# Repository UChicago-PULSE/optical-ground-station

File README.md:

This repository contains files from the Optical Ground Station.
  - Polarimeter Data Collection Contains data obtained from Polarimeter experiments and code to parse that data written by Juan Prieto
  - Telescope Control contains code to control the telescope and point it according to a predetermined path. Written by Rodrigo Spinola e Castro
  - Camera Control will have code to interface with the tracking camera. Written by Ashley Ashiku and Juan Prieto
  - Comparator will have KiCad 9.0 files for the OGS comparator circuit. Designed by Juan Prieto

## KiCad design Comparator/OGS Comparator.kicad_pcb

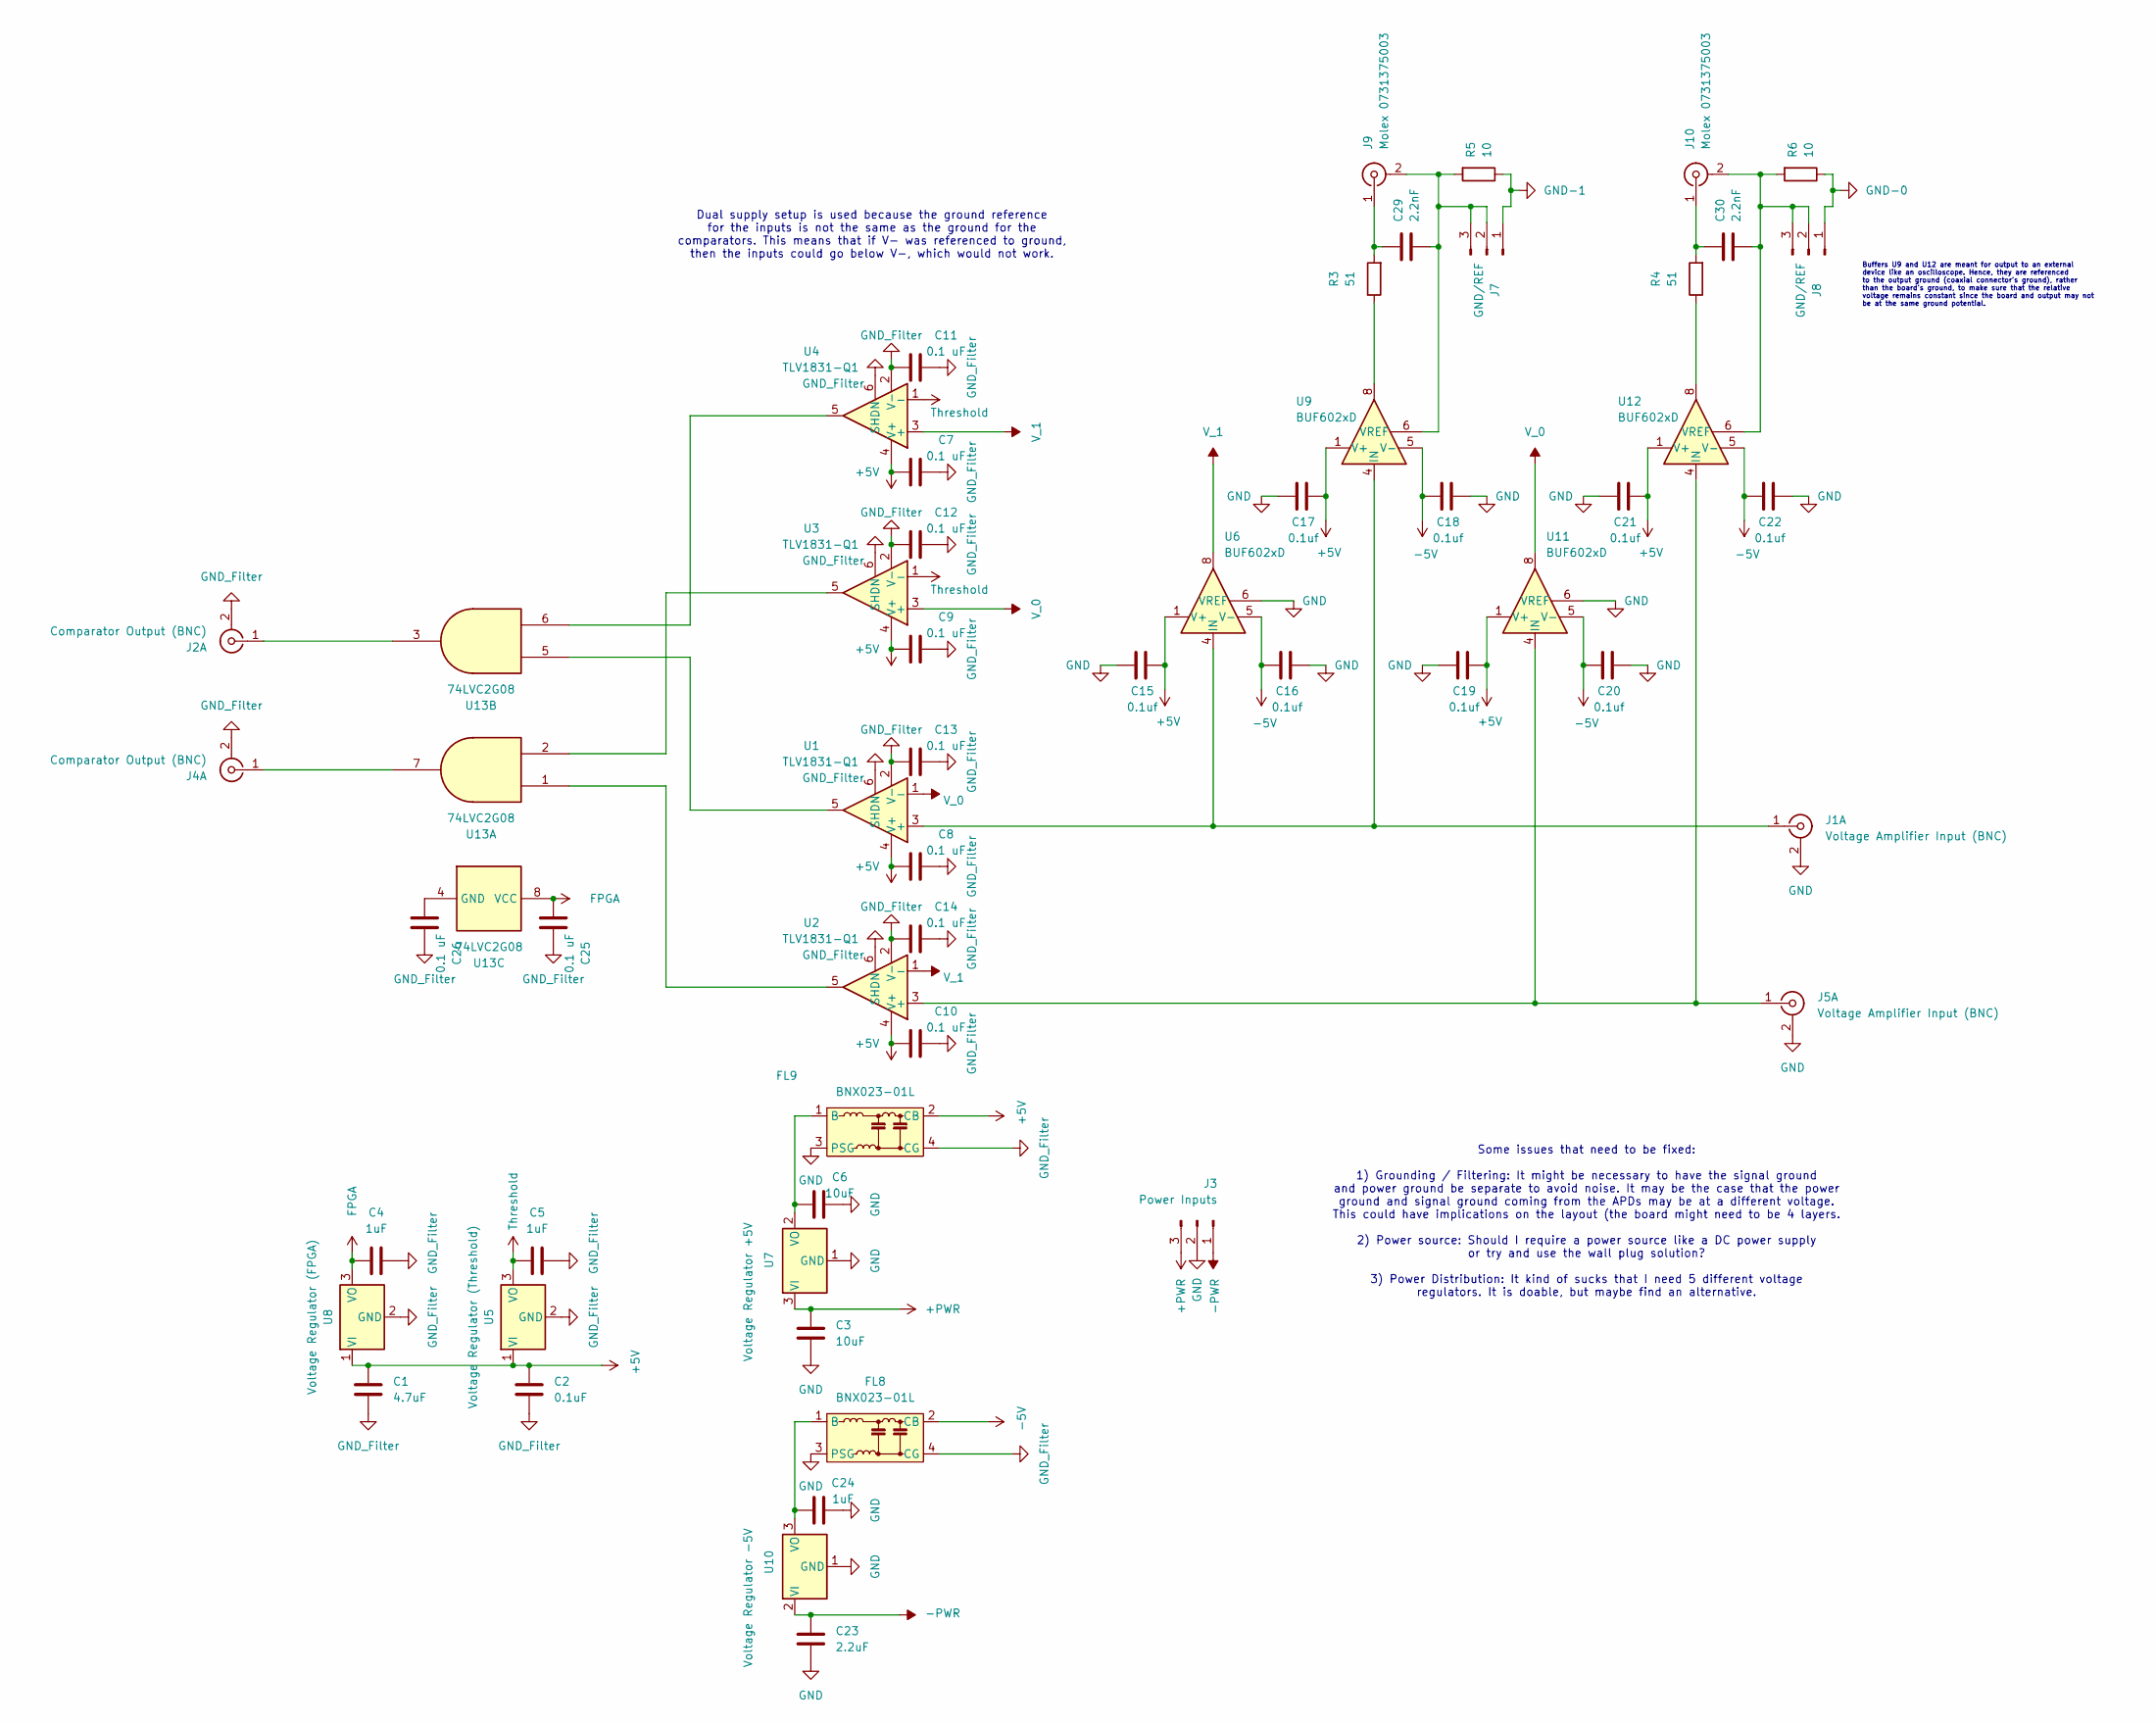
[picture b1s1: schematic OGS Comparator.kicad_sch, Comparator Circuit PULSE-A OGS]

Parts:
C1: 4.7uF; C_0805_2012Metric
C2: 0.1uF; C_0805_2012Metric
C3, C6: 10uF; C_0805_2012Metric
C4, C5, C24: 1uF; C_0805_2012Metric
C7, C8, C9, C10, C11, C12, C13, C14, C25, C26: 0.1 uF; C_0805_2012Metric
C15, C16, C17, C18, C19, C20, C21, C22: 0.1uf; C_0805_2012Metric
C23: 2.2uF; C_0805_2012Metric
C29, C30: 2.2nF; C_0805_2012Metric; LCSC Part # C28260
FL8, FL9: BNX023-01L; Filter_Murata_BNX025
J1, J5: Voltage Amplifier Input (BNC); Molex BNC
J2, J4: Comparator Output (BNC); Molex BNC
J3: Power Inputs; JST_EH_B3B-EH-A_1x03_P2.50mm_Vertical
J7, J8: GND/REF; PinHeader_1x03_P2.54mm_Vertical
J9, J10: Molex 0731375003; Molex BNC
R3, R4: 51; R_0805_2012Metric; LCSC Part # C17738
R5, R6: 10; R_0805_2012Metric; LCSC C25278
U1, U2, U3, U4: TLV1831-Q1; SOT-23-6
U5: Voltage Regulator (Threshold); TO-220-3_Vertical
U6, U9, U11, U12: BUF602xD; SOIC-8_3.9x4.9mm_P1.27mm
U7: Voltage Regulator +5V; TO-220-3_Vertical
U8: Voltage Regulator (FPGA); TO-220-3_Vertical
U10: Voltage Regulator -5V; TO-220-3_Vertical
U13: 74LVC2G08; VSSOP-8_2.3x2mm_P0.5mm

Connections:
+5V: C1.1, C2.1, C7.1, C8.1, C9.1, C10.1, C15.2, C17.2, C19.2, C21.2, FL9.2 (CB), U1.4 (V+), U2.4 (V+), U3.4 (V+), U4.4 (V+), U5.1 (VI), U6.1 (V+), U8.1 (VI), U9.1 (V+), U11.1 (V+), U12.1 (V+)
+PWR: C3.1, J3.3, U7.3 (VI)
-5V: C16.1, C18.1, C20.1, C22.1, FL8.2 (CB), U6.5 (V-), U9.5 (V-), U11.5 (V-), U12.5 (V-)
-PWR: C23.1, J3.1, U10.2 (VI)
FPGA: C4.1, C25.1, U8.3 (VO), U13.8 (VCC)
GND: C3.2, C6.2, C15.1, C16.2, C17.1, C18.2, C19.1, C20.2, C21.1, C22.2, C23.2, C24.2, FL8.3 (PSG), FL9.3 (PSG), J1.2 (Ext1), J3.2, J5.2 (Ext1), U6.6 (VREF), U7.1 (GND), U10.1 (GND), U11.6 (VREF)
GND-0: J8.1, R6.1
GND-1: J7.1, R5.1
GND_Filter: C1.2, C2.2, C4.2, C5.2, C7.2, C8.2, C9.2, C10.2, C11.1, C11.2, C12.1, C12.2, C13.1, C13.2, C14.1, C14.2, C25.2, C26.2, FL8.4 (CG), FL9.4 (CG), J2.2 (Ext1), J4.2 (Ext1), U1.2 (V-), U1.6 (SHDN), U2.2 (V-), U2.6 (SHDN), U3.2 (V-), U3.6 (SHDN), U4.2 (V-), U4.6 (SHDN), U5.2 (GND), U8.2 (GND)
unnamed: C24.1, FL8.1 (B), U10.3 (VO)
unnamed: C6.1, FL9.1 (B), U7.2 (VO)
unnamed: J1.1 (In1), U1.3 (+), U6.4 (IN), U9.4 (IN)
unnamed: J2.1 (In1), U13.3
unnamed: J4.1 (In1), U13.7
unnamed: J5.1 (In1), U2.3 (+), U11.4 (IN), U12.4 (IN)
unnamed: C29.2, J7.2, J7.3, J9.2 (Ext), R5.2, U9.6 (VREF)
unnamed: C29.1, J9.1 (In), R3.2
unnamed: C30.2, J8.2, J8.3, J10.2 (Ext), R6.2, U12.6 (VREF)
unnamed: C30.1, J10.1 (In), R4.2
unnamed: R3.1, U9.8
unnamed: R4.1, U12.8
unnamed: U1.5, U13.5
unnamed: U2.5, U13.1
unnamed: U3.5, U13.2
unnamed: U4.5, U13.6
unnamed: C26.1, U13.4 (GND)
Threshold: C5.1, U3.1 (-), U4.1 (-), U5.3 (VO)
V_0: U1.1 (-), U3.3 (+), U11.8
V_1: U2.1 (-), U4.3 (+), U6.8

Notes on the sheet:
Dual supply setup is used because the ground reference for the inputs is not the same as the ground for the comparators. This means that if V- was referenced to ground, then the inputs could go below V-, which would not work.
Some issues that need to be fixed: 1) Grounding / Filtering: It might be necessary to have the signal ground and power ground be separate to avoid noise. It may be the case that the power ground and signal ground coming from the APDs may be at a different voltage. This could have implications on th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
Buffers U9 and U12 are meant for output to an external device like an oscilloscope. Hence, they are referenced to the output ground (coaxial connector's ground), rather than the board's ground, to make sure that the relative voltage remains constant since the board and output may not be at the same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

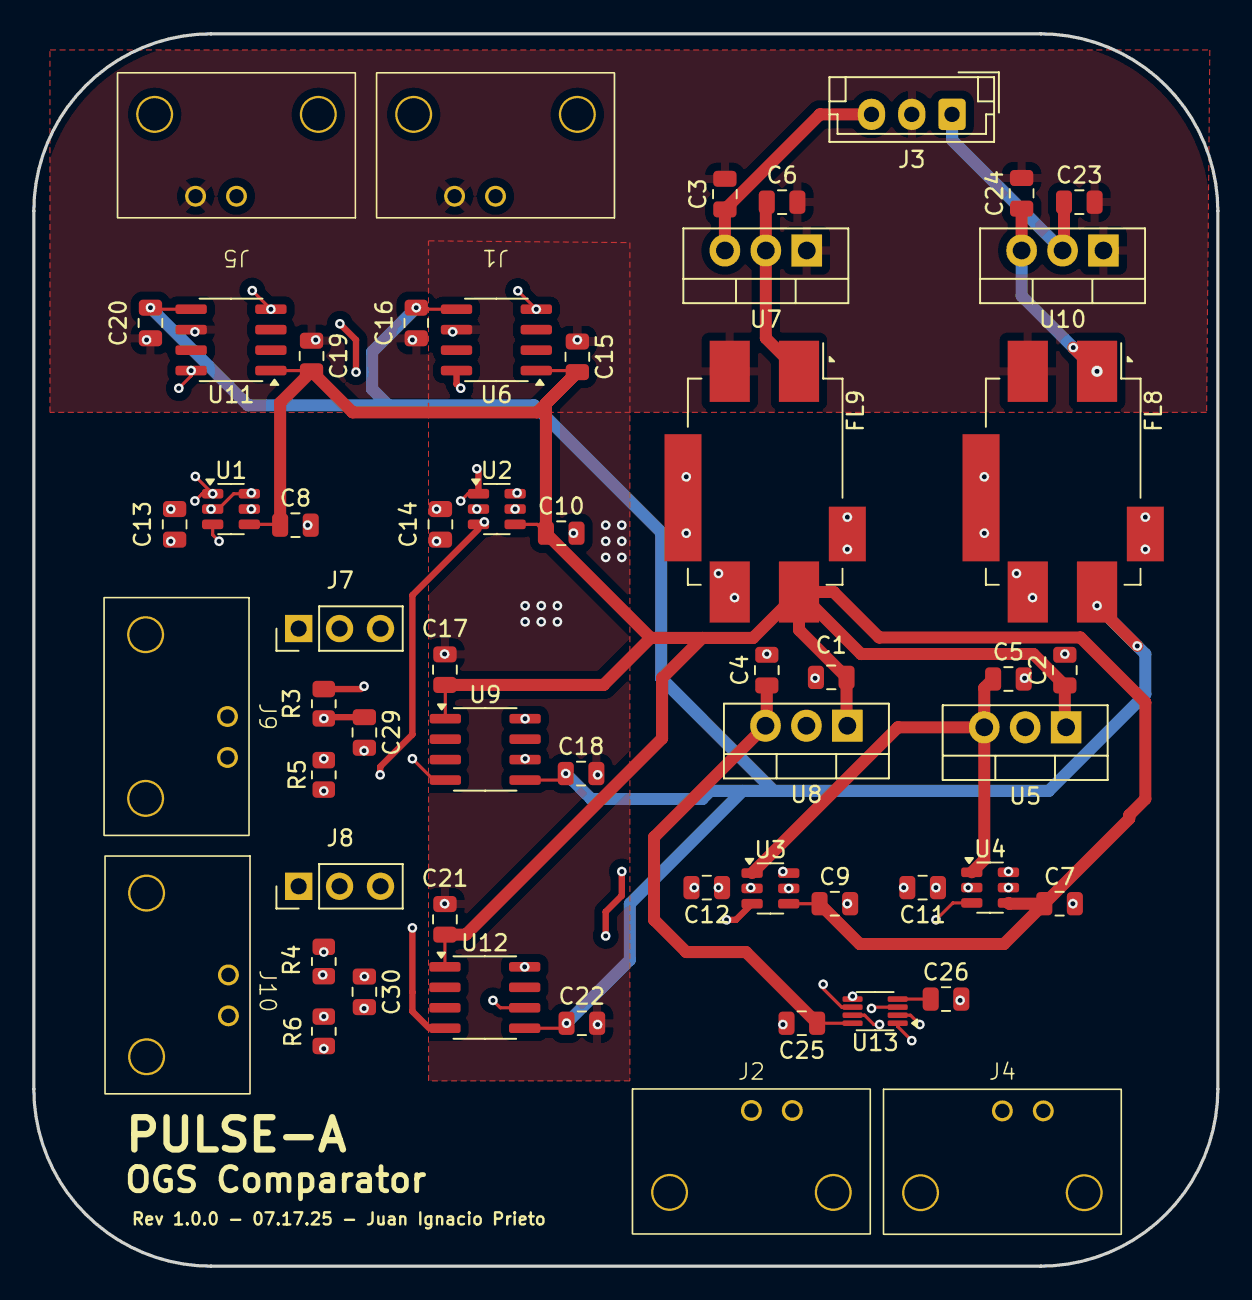
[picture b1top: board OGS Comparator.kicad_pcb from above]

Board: 4 copper layers, 73.5 x 76.5 mm, 56 parts (0 on the bottom side), 29 nets.

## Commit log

2024-10-12 Josh fixed a term that was not there in the previous version
2024-10-13 Add files via upload
    This version now includes the astropy code for what the alt and az angles actually are.
2025-02-16 Added polarimeter data collection python files
2025-02-16 Updated class. Still need to make some more methods, but most of it is done
2025-02-16 forgot to commit extra file
2025-02-17 Added average method
2025-02-17 Added standard deviation method
2025-02-22 Added function to read multiple files from single directory
2025-02-23 Edited to create measurement objects. Issues with ordering based on name, but should not matter much.
2025-02-23 Update README.md
    Finally got around to fixing this readme file
2025-02-23 Delete nexstar.py
    Cleanup
2025-02-23 Delete commandscript.py
    Cleanup
2025-02-23 Delete Slew Rate Calculations.ipynb
    Cleanup
2025-02-23 Delete CelestronControlApp.py
    Cleanup
2025-02-23 Delete Pulse directory
    Cleanup
2025-02-23 Organizing the github
2025-02-23 cleanup
2025-02-24 Added histogram plot
2025-02-24 Added plots
2025-02-25 I forgor what I added but some graph prob
2025-02-26 Made new plots / functions
2025-02-27 Fixed plots
2025-02-27 Made more graphs, fixed graph func
2025-03-01 create notes area
2025-03-01 add camera desc
2025-03-01 start readme
2025-03-02 Updating OGS_control_class
2025-03-02 Creating tracking_methods_records file
    Also include first March 2nd 2025 update with data
2025-03-02 Added intended path function form
2025-03-03 Lab meeting plots and shi
2025-03-27 initial to do list
2025-03-29 Work done march 29th
    Fixed some stuff with the get azm_alt that kept getting me values no between 0-360 degrees. Tested many correction factors.
2025-03-30 march 30th update with RMS vs correction factor plot
2025-04-01 Removed camera manual link
2025-04-05 Added Ashley goals + resource
2025-04-06 Added resources
2025-04-13 Apr 13th update
    First try at a go-to function
2025-04-13 Uploading ashley camera communication code
2025-04-13 Uploading python wrapper for camera code
2025-04-13 Uploading FITS interpretation code
2025-04-13 Uploading jupyter for FITS interpretation
2025-04-27 Update for APR 26th tests.
    Tested on a simulated pass! Pickle file contains pass info.
2025-04-30 init_interface
2025-04-30 file_distribution
2025-04-30 Stop tracking .DS_Store files
2025-05-03 Added overlays and analyzed some data
2025-05-03 Worksession05032025
2025-05-04 Changed code for pure connection
2025-05-04 Camera picture only code
2025-05-09 Added files
2025-05-09 Tested and fixed existing code
2025-05-11 pipeline_to_send.py
2025-05-11 Moved pipeline_to_send.py to Polarimeter Data Collection
2025-05-11 final
2025-05-25 Plots for Paper
2025-06-16 Small changes plotting stuff
2025-07-10 Unknown updates
2025-07-10 Commented out camera code
2025-07-10 Reorganizing folder
2025-07-10 Delete Camera Control/.DS_Store
    What is this I don't know
2025-07-22 Commented out error code
2025-08-18 Added comparator V.01 files
2025-09-15 Polarization analysis for telescope experiment
2025-09-24 Add files via upload
    Translates the 42 data into the angle and plane of incidence which will be used for the PAT simulations.
2025-09-24 Add files via upload
    Takes in angles calculated for 42 data and runs ray traces for each timestamp. Returns centroid data in a csv file
2025-09-24 changed the file path
2025-09-25 Update PAT_OGS_SOURCE_CODE.m
    Runs every single time stamp instead of only the first 50
2025-09-29 Moved zemax files into its own dir
2025-10-02 Added zemax PAT analysis files and data files
2025-10-02 Deleted 0.5 degree pointing error file that was wrong
2025-10-02 Update in Zemax sim
2025-10-04 Added correlation
2025-10-04 Added Title and Legend
2025-10-04 Bunch of files got deleted so I re-added them
2025-10-04 Added labels to graphs
